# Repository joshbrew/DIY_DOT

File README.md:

# DIY Diffuse Optical Tomography (DOT) PCB plans

Testing low cost 28 sensor DOT. This repo will be getting updated as I get results and some working code to share. I will share how to drive the LEDs and how I get simultaneous sensor output as I get things demonstrable.

DIY DOT flexible sensor design based on [this 2007 Retinotopic mapping paper](https://www.pnas.org/content/104/29/12169) for a simple and modular 28 channel high-density optical tomography headset. The question I want to answer: can I get [deep image reconstruction](https://journals.plos.org/ploscompbiol/article?id=10.1371/journal.pcbi.1006633)?

This design uses 28 OPT101s and 24 pairs (48 total) 1206 sized generic LED pairs of whatever wavelength you want. The OPT101s can have the gain turned up by adding a cap and resistor between the right pins [see datasheet](https://www.ti.com/lit/ds/symlink/opt101.pdf?HQS=TI-null-null-alldatasheets-df-pf-SEP-wwe). You can get really cheap ones on Aliexpress that work consistently.

Use a site like PCBway for cheap flex PCBs. There is FR4 stiffener on both sides. This is meant to be hand-assembled, careful not to burn the pads or sensitive OPT101 pins (i.e. use low temperature solder for testing). Pop the OPT101s (notch facing left from the front) in through the back to make them flush with the stiffener and solder from back.  

# 16 channel (forehead-friendly)

New (cheapo version):

New (includes transimpedance amps):

Old:

# For LED Driver we're using the $4 RP2040 mini, drivers WIP and docs etc.

# WIP Software for capture and simulation:

3D simulation with BabylonJS:
- https://github.com/joshbrew/DIY_DOT/tree/main/js/bananas
Recording test for our nRF5x boards (WIP connector/carrier board incoming after we test it):
- https://github.com/joshbrew/DIY_DOT/tree/main/js/record_nirs

The simulation math needs help but we'll figure it out eventually.

### What you need to make it work:
* LED driver microcontroller with PWM driver, we've got a WIP firmware for the RP2040 
* 48 GPIO or some kind of relay to drive the LEDs which need to be flashed independently. Can be done by stringing multiple cheap boards together via RX/TX pins (will publish examples eventually). 
* We recommend narrow-coned LEDs to minimize scalp interference for short separation channels.
* Add light pipes over PD and LED areas to get better contact.
* [Use >1000nm IR LEDs for best penetration. (no idea if they exist at this size)](https://www.spiedigitallibrary.org/journals/journal-of-biomedical-optics/volume-25/issue-09/097003/Diffuse-correlation-spectroscopy-measurements-of-blood-flow-using-1064nm-light/10.1117/1.JBO.25.9.097003.full?fbclid=IwAR02-l_q-xCykuuqUjc_RWJfQE7ESOEIRK0G9mqZSWaGiFhfwu1QNV42vjQ&SSO=1) The other LED can be red, green, or another IR wavelength (e.g. 850nm).

## What can I do with this?

Read about fMRI, then assume this is an fMRI but it's dirt cheap in comparison. However, it only gets you the few outer centimeters of depth resolution, which can be enhanced with higher power lighting, guassian windows, interferometry (the most interesting next logical step for this ala OCT), and some other classic filtering tricks from RF and astronomy. So we can do legit mind reading, source localization for EEG, brain topology studies, and potentially real time monitoring of problems like subdural hematoma or possible metabolic issues in the high energy-demanding neocortex. Multimodal imaging promises to solve a lot of modeling problems with this technology, and there's probably a lot more to learn just in terms of how different physiology contains relevant computational information and what the interplay is. That's my very unqualified 2 cents :P

## License 
MIT License: Do whatever you want with it, I'm gonna do what I want with it too. And cite this repo if you make it useful! 
Get in touch @ brewster.joshua1@gmail.com, I'm working on a scalable version of this stuff but it just takes forever between factory times and me not knowing what the hell I'm doing.

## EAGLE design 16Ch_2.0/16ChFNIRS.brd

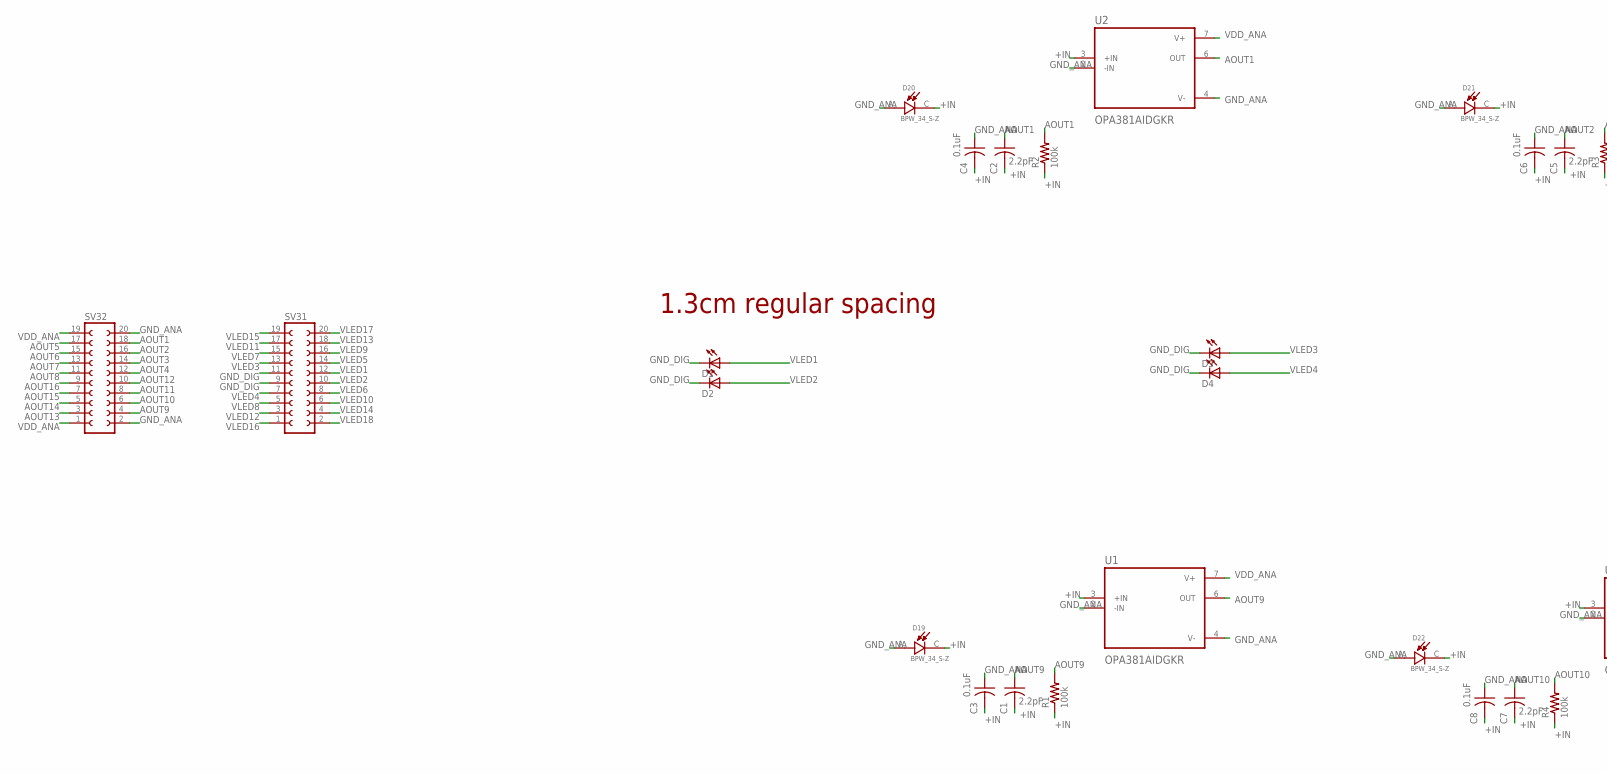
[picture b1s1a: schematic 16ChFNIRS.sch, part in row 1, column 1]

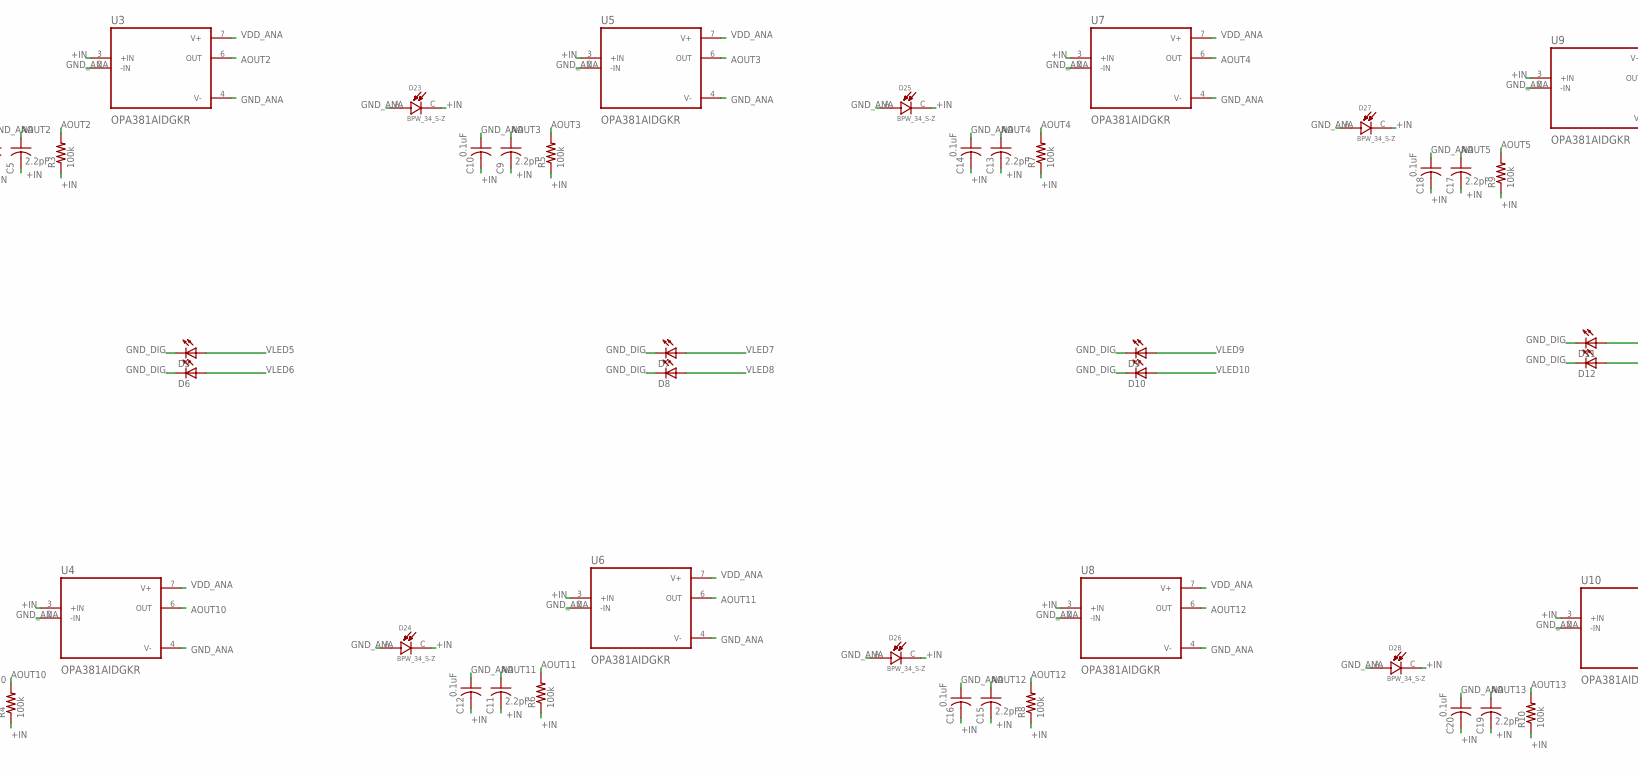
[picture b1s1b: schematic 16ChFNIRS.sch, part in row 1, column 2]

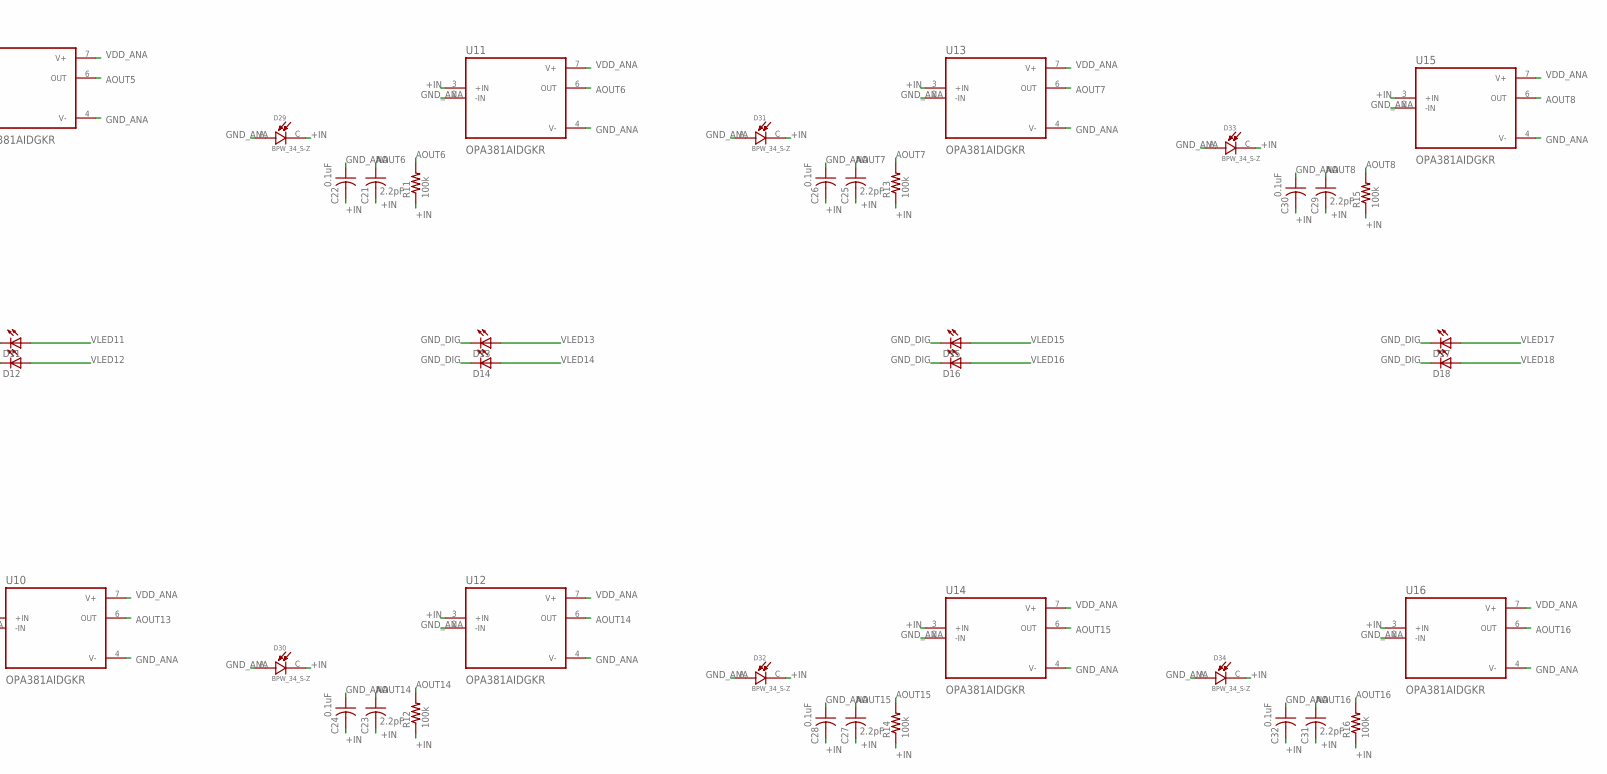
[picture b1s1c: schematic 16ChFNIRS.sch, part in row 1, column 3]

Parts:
C1, C2, C5, C7, C9, C11, C13, C15, C17, C19, C21, C23, C25, C27, C29, C31: 2.2pF; C0603K
C3, C4, C6, C8, C10, C12, C14, C16, C18, C20, C22, C24, C26, C28, C30, C32: 0.1uF; C0603K
D1, D2, D3, D4, D5, D6, D7, D8, D9, D10, D11, D12, D13, D14, D15, D16, D17, D18: LED1206; LED-1206
D19, D20, D21, D22, D23, D24, D25, D26, D27, D28, D29, D30, D31, D32, D33, D34: BPW_34_S-Z; DIO_BPW_34_S-Z
R1, R2, R3, R4, R5, R6, R7, R8, R9, R10, R11, R12, R13, R14, R15, R16: 100k; R0603
SV31, SV32: FE10-2
U1, U2, U3, U4, U5, U6, U7, U8, U9, U10, U11, U12, U13, U14, U15, U16: OPA381AIDGKR; SOP65P490X110-8N

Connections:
+IN: C1.2, C2.2, C3.2, C4.2, C5.2, C6.2, C7.2, C8.2, C9.2, C10.2, C11.2, C12.2, C13.2, C14.2, C15.2, C16.2, C17.2, C18.2, C19.2, C20.2, C21.2, C22.2, C23.2, C24.2, C25.2, C26.2, C27.2, C28.2, C29.2, C30.2, C31.2, C32.2, D19.C, D20.C, D21.C, D22.C, D23.C, D24.C, D25.C, D26.C, D27.C, D28.C, D29.C, D30.C, D31.C, D32.C, D33.C, D34.C, R1.1, R2.1, R3.1, R4.1, R5.1, R6.1, R7.1, R8.1, R9.1, R10.1, R11.1, R12.1, R13.1, R14.1, R15.1, R16.1, U1.3 (+IN), U2.3 (+IN), U3.3 (+IN), U4.3 (+IN), U5.3 (+IN), U6.3 (+IN), U7.3 (+IN), U8.3 (+IN), U9.3 (+IN), U10.3 (+IN), U11.3 (+IN), U12.3 (+IN), U13.3 (+IN), U14.3 (+IN), U15.3 (+IN), U16.3 (+IN)
AOUT1: C2.1, R2.2, SV32.18, U2.6 (OUT)
AOUT2: C5.1, R3.2, SV32.16, U3.6 (OUT)
AOUT3: C9.1, R5.2, SV32.14, U5.6 (OUT)
AOUT4: C13.1, R7.2, SV32.12, U7.6 (OUT)
AOUT5: C17.1, R9.2, SV32.17, U9.6 (OUT)
AOUT6: C21.1, R11.2, SV32.15, U11.6 (OUT)
AOUT7: C25.1, R13.2, SV32.13, U13.6 (OUT)
AOUT8: C29.1, R15.2, SV32.11, U15.6 (OUT)
AOUT9: C1.1, R1.2, SV32.4, U1.6 (OUT)
AOUT10: C7.1, R4.2, SV32.6, U4.6 (OUT)
AOUT11: C11.1, R6.2, SV32.8, U6.6 (OUT)
AOUT12: C15.1, R8.2, SV32.10, U8.6 (OUT)
AOUT13: C19.1, R10.2, SV32.3, U10.6 (OUT)
AOUT14: C23.1, R12.2, SV32.5, U12.6 (OUT)
AOUT15: C27.1, R14.2, SV32.7, U14.6 (OUT)
AOUT16: C31.1, R16.2, SV32.9, U16.6 (OUT)
GND_ANA: C3.1, C4.1, C6.1, C8.1, C10.1, C12.1, C14.1, C16.1, C18.1, C20.1, C22.1, C24.1, C26.1, C28.1, C30.1, C32.1, D19.A, D20.A, D21.A, D22.A, D23.A, D24.A, D25.A, D26.A, D27.A, D28.A, D29.A, D30.A, D31.A, D32.A, D33.A, D34.A, SV32.2, SV32.20, U1.2 (-IN), U1.4 (V-), U2.2 (-IN), U2.4 (V-), U3.2 (-IN), U3.4 (V-), U4.2 (-IN), U4.4 (V-), U5.2 (-IN), U5.4 (V-), U6.2 (-IN), U6.4 (V-), U7.2 (-IN), U7.4 (V-), U8.2 (-IN), U8.4 (V-), U9.2 (-IN), U9.4 (V-), U10.2 (-IN), U10.4 (V-), U11.2 (-IN), U11.4 (V-), U12.2 (-IN), U12.4 (V-), U13.2 (-IN), U13.4 (V-), U14.2 (-IN), U14.4 (V-), U15.2 (-IN), U15.4 (V-), U16.2 (-IN), U16.4 (V-)
GND_DIG: D1.C, D2.C, D3.C, D4.C, D5.C, D6.C, D7.C, D8.C, D9.C, D10.C, D11.C, D12.C, D13.C, D14.C, D15.C, D16.C, D17.C, D18.C, SV31.9, SV31.11
VDD_ANA: SV32.1, SV32.19, U1.7 (V+), U2.7 (V+), U3.7 (V+), U4.7 (V+), U5.7 (V+), U6.7 (V+), U7.7 (V+), U8.7 (V+), U9.7 (V+), U10.7 (V+), U11.7 (V+), U12.7 (V+), U13.7 (V+), U14.7 (V+), U15.7 (V+), U16.7 (V+)
VLED1: D1.A, SV31.12
VLED2: D2.A, SV31.10
VLED3: D3.A, SV31.13
VLED4: D4.A, SV31.7
VLED5: D5.A, SV31.14
VLED6: D6.A, SV31.8
VLED7: D7.A, SV31.15
VLED8: D8.A, SV31.5
VLED9: D9.A, SV31.16
VLED10: D10.A, SV31.6
VLED11: D11.A, SV31.17
VLED12: D12.A, SV31.3
VLED13: D13.A, SV31.18
VLED14: D14.A, SV31.4
VLED15: D15.A, SV31.19
VLED16: D16.A, SV31.1
VLED17: D17.A, SV31.20
VLED18: D18.A, SV31.2

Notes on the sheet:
1.3cm regular spacing

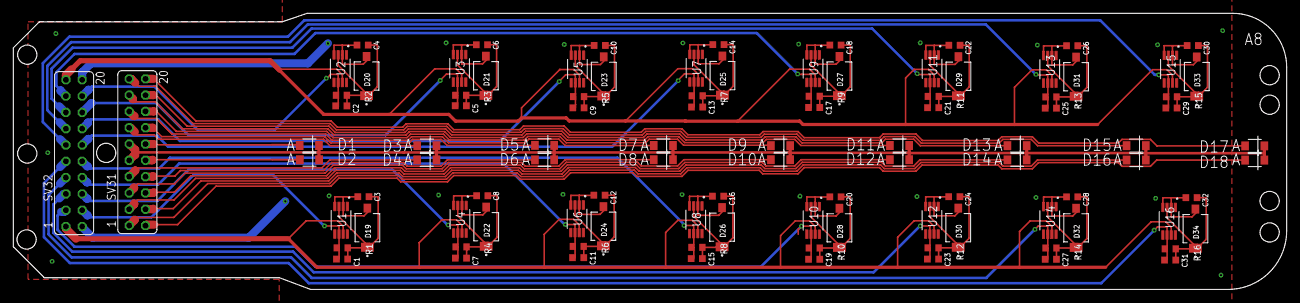
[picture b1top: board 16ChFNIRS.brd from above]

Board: 2 copper layers, 198.4 x 43.0 mm, 100 parts (0 on the bottom side), 38 nets.

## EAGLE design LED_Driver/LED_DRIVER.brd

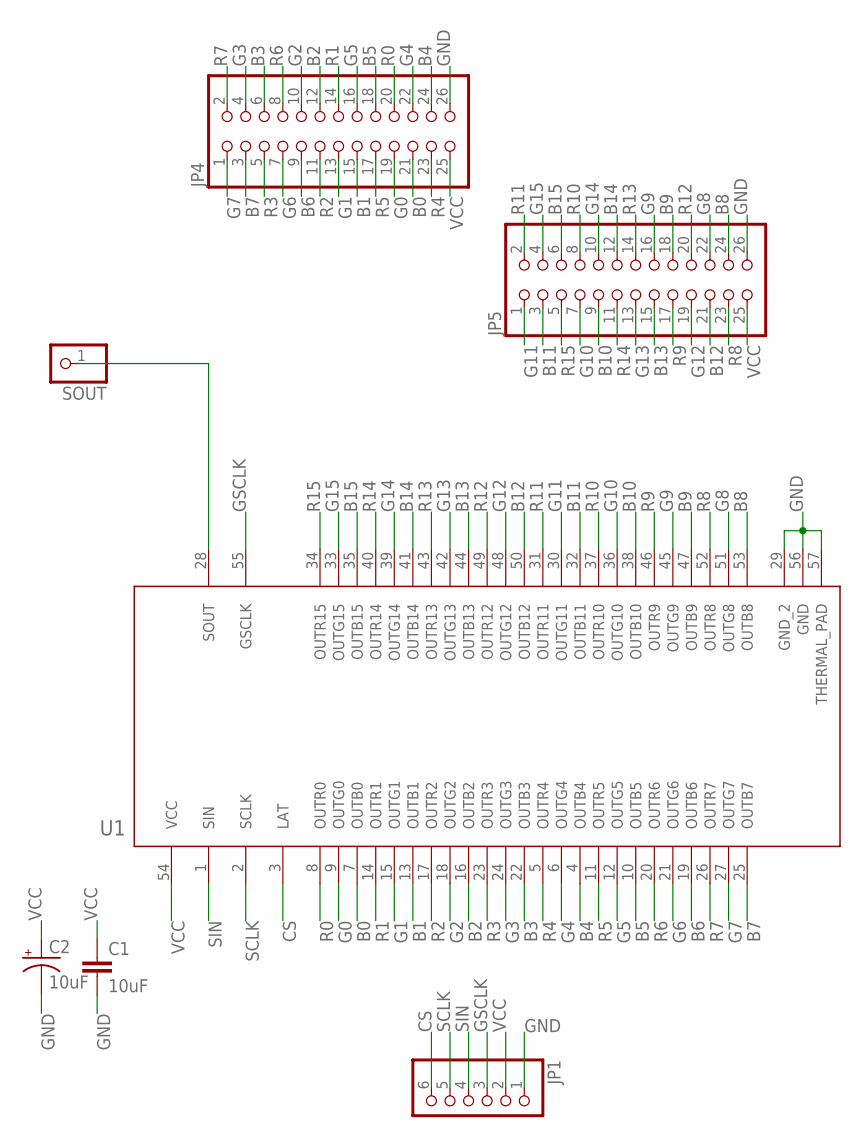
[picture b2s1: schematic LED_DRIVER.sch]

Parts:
C1: 10uF; C0603
C2: 10uF; E2-4
JP1: PINHD-1X6; 1X06
JP4, JP5: PINHD-2X13; 2X13
SOUT: PINHD-1X1; 1X01
U1: Value; DCA0056F-IPC_B

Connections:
B0: JP4.21, U1.7 (OUTB0)
B1: JP4.15, U1.13 (OUTB1)
B2: JP4.12, U1.16 (OUTB2)
B3: JP4.6, U1.22 (OUTB3)
B4: JP4.24, U1.4 (OUTB4)
B5: JP4.18, U1.10 (OUTB5)
B6: JP4.9, U1.19 (OUTB6)
B7: JP4.3, U1.25 (OUTB7)
B8: JP5.24, U1.53 (OUTB8)
B9: JP5.18, U1.47 (OUTB9)
B10: JP5.9, U1.38 (OUTB10)
B11: JP5.3, U1.32 (OUTB11)
B12: JP5.21, U1.50 (OUTB12)
B13: JP5.15, U1.44 (OUTB13)
B14: JP5.12, U1.41 (OUTB14)
B15: JP5.6, U1.35 (OUTB15)
CS: JP1.6, U1.3 (LAT)
G0: JP4.19, U1.9 (OUTG0)
G1: JP4.13, U1.15 (OUTG1)
G2: JP4.10, U1.18 (OUTG2)
G3: JP4.4, U1.24 (OUTG3)
G4: JP4.22, U1.6 (OUTG4)
G5: JP4.16, U1.12 (OUTG5)
G6: JP4.7, U1.21 (OUTG6)
G7: JP4.1, U1.27 (OUTG7)
G8: JP5.22, U1.51 (OUTG8)
G9: JP5.16, U1.45 (OUTG9)
G10: JP5.7, U1.36 (OUTG10)
G11: JP5.1, U1.30 (OUTG11)
G12: JP5.19, U1.48 (OUTG12)
G13: JP5.13, U1.42 (OUTG13)
G14: JP5.10, U1.39 (OUTG14)
G15: JP5.4, U1.33 (OUTG15)
GND: C1.2, C2.-, JP1.1, JP4.26, JP5.26, U1.29 (GND_2), U1.56 (GND), U1.57 (THERMAL_PAD)
GSCLK: JP1.3, U1.55 (GSCLK)
R0: JP4.20, U1.8 (OUTR0)
R1: JP4.14, U1.14 (OUTR1)
R2: JP4.11, U1.17 (OUTR2)
R3: JP4.5, U1.23 (OUTR3)
R4: JP4.23, U1.5 (OUTR4)
R5: JP4.17, U1.11 (OUTR5)
R6: JP4.8, U1.20 (OUTR6)
R7: JP4.2, U1.26 (OUTR7)
R8: JP5.23, U1.52 (OUTR8)
R9: JP5.17, U1.46 (OUTR9)
R10: JP5.8, U1.37 (OUTR10)
R11: JP5.2, U1.31 (OUTR11)
R12: JP5.20, U1.49 (OUTR12)
R13: JP5.14, U1.43 (OUTR13)
R14: JP5.11, U1.40 (OUTR14)
R15: JP5.5, U1.34 (OUTR15)
SCLK: JP1.5, U1.2 (SCLK)
SIN: JP1.4, U1.1 (SIN)
SOUT: SOUT.1, U1.28 (SOUT)
VCC: C1.1, C2.+, JP1.2, JP4.25, JP5.25, U1.54 (VCC)

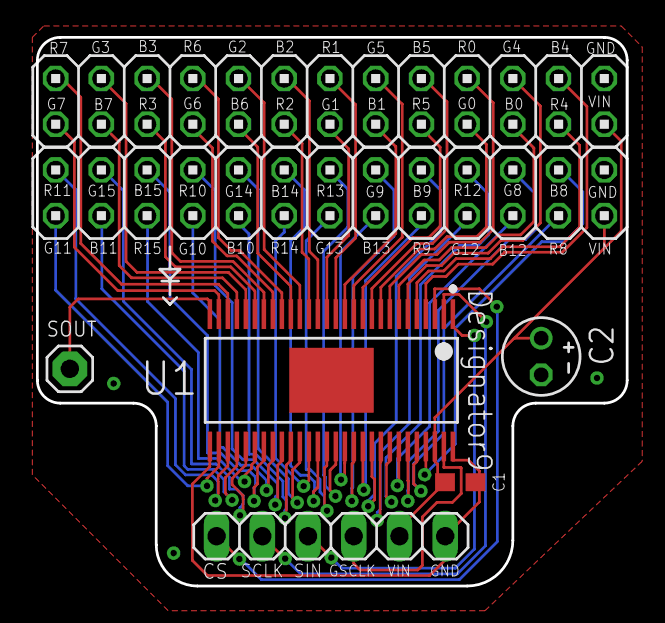
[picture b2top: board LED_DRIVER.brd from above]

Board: 2 copper layers, 32.8 x 30.5 mm, 7 parts (0 on the bottom side), 55 nets.

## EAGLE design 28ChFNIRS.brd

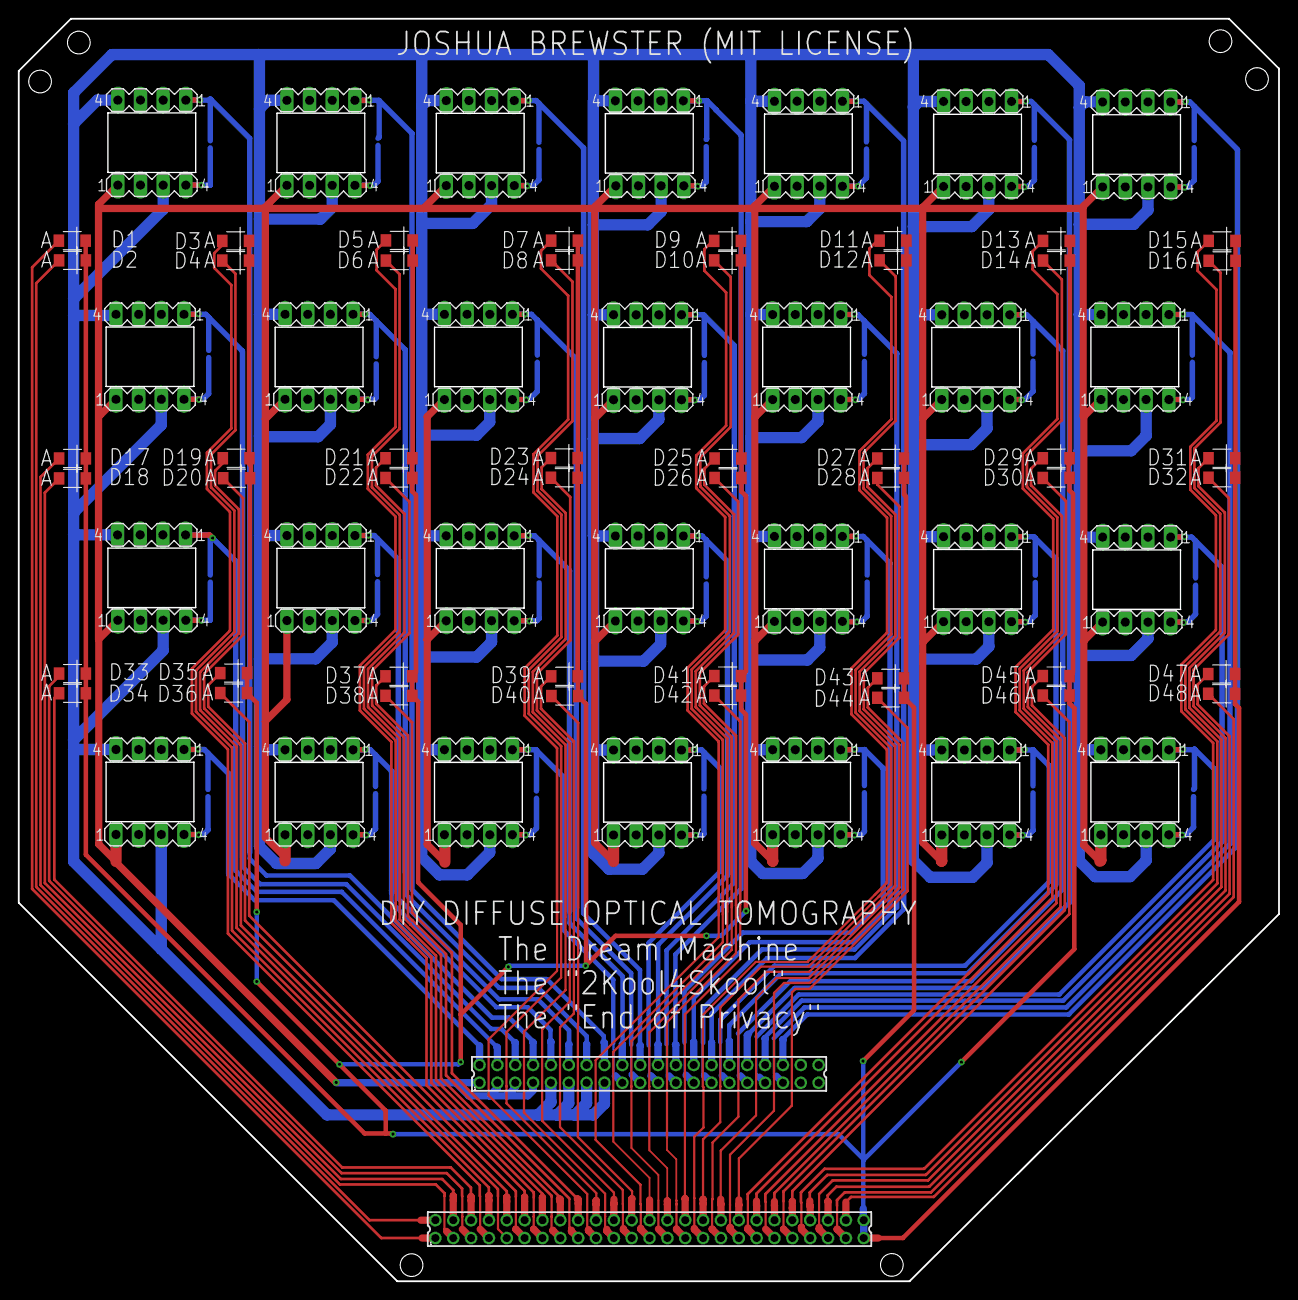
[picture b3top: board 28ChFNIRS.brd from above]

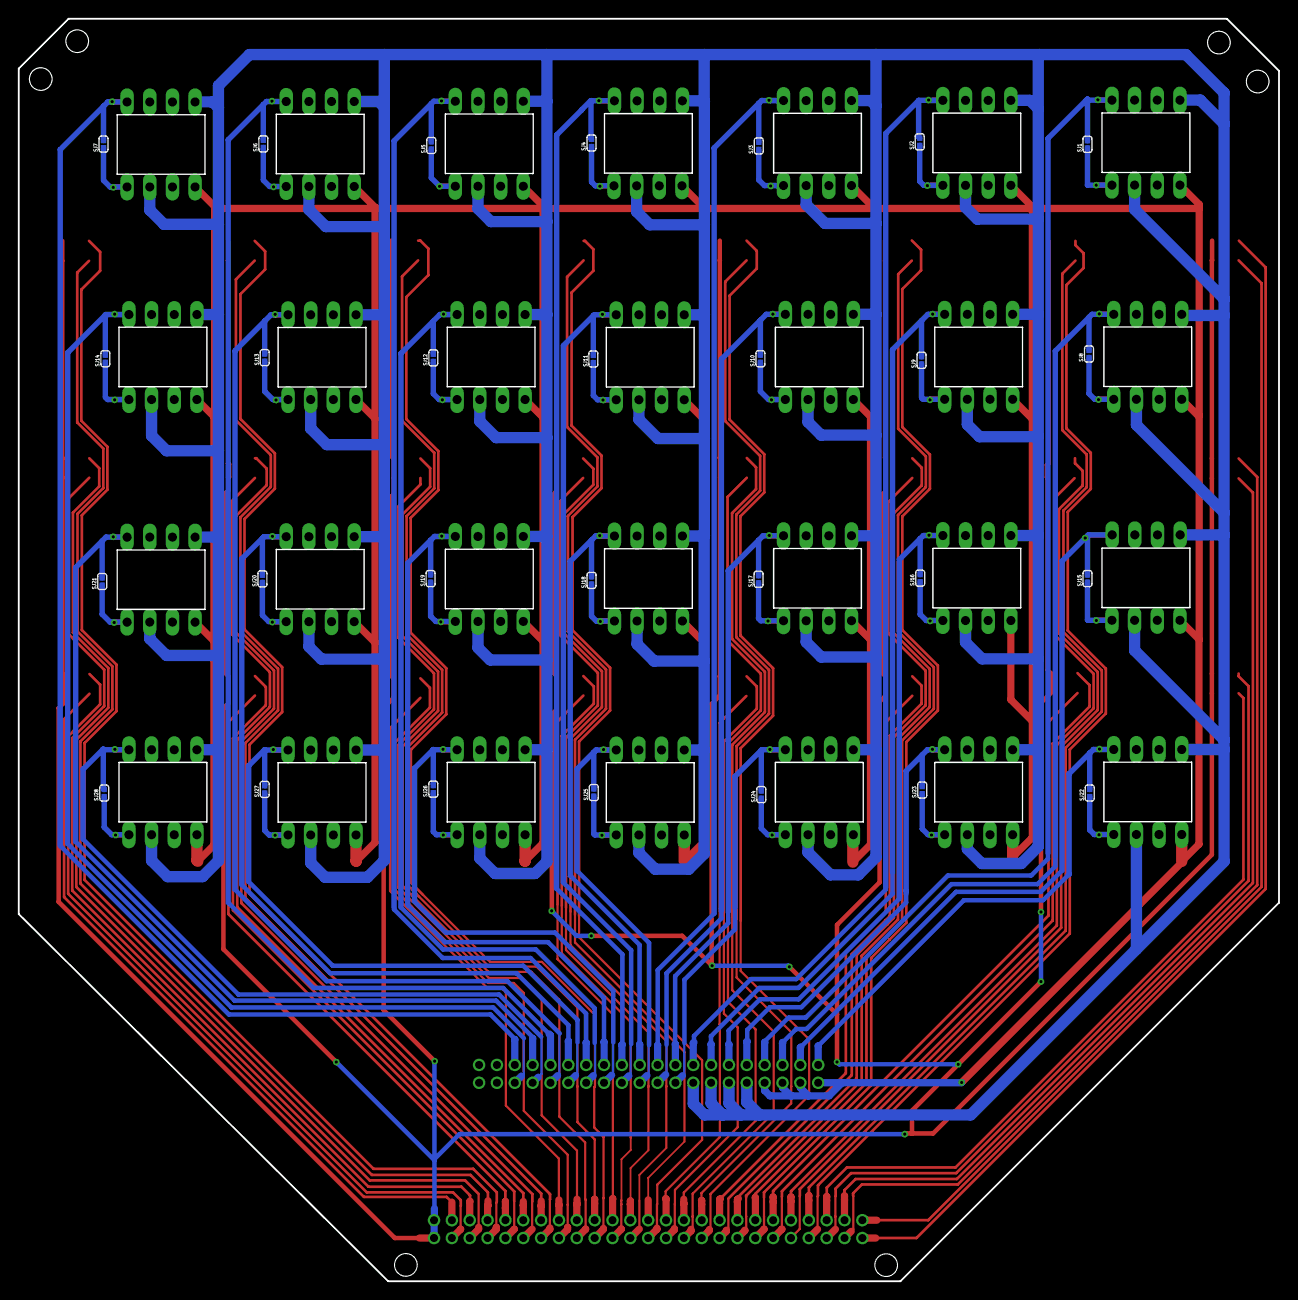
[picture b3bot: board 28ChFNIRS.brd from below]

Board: 2 copper layers, 141.2 x 141.5 mm, 134 parts (28 on the bottom side), 107 nets.

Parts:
D1, D2, D3, D4, D5, D6, D7, D8, D9, D10, D11, D12, D13, D14, D15, D16, D17, D18, D19, D20, D21, D22, D23, D24, D25, D26, D27, D28, D29, D30, D31, D32, D33, D34, D35, D36, D37, D38, D39, D40, D41, D42, D43, D44, D45, D46, D47, D48: LED-1206
SJ1, SJ2, SJ3, SJ4, SJ5, SJ6, SJ7, SJ8, SJ9, SJ10, SJ11, SJ12, SJ13, SJ14, SJ15, SJ16, SJ17, SJ18, SJ19, SJ20, SJ21, SJ22, SJ23, SJ24, SJ25, SJ26, SJ27, SJ28: SOLDERJUMPERNC; SJ_2S_SMALL
SV1, SV2, SV3, SV4, SV5, SV6, SV7, SV8, SV9, SV10, SV11, SV12, SV13, SV14, SV15, SV16, SV17, SV18, SV19, SV20, SV21, SV22, SV23, SV24, SV25, SV26, SV27, SV28, SV29, SV30, SV31, SV32, SV33, SV34, SV35, SV36, SV37, SV38, SV39, SV40, SV41, SV42, SV43, SV44, SV45, SV46, SV47, SV48, SV49, SV50, SV51, SV52, SV53, SV54, SV55, SV56: MA04-1
X1: 332-50
X2: 87758-4016

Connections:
AOUT1: SJ1.2, SV1.1, X2.8
AOUT2: SJ2.2, SV3.1, X2.16
AOUT3: SJ3.2, SV5.1, X2.20
AOUT4: SJ4.2, SV7.1, X2.24
AOUT5: SJ5.2, SV9.1, X2.28
AOUT6: SJ6.2, SV11.1, X2.32
AOUT7: SJ7.2, SV13.1, X2.36
AOUT8: SJ8.2, SV15.1, X2.6
AOUT9: SJ9.2, SV17.1, X2.14
AOUT10: SJ10.2, SV19.1, X2.19
AOUT11: SJ11.2, SV21.1, X2.23
AOUT12: SJ12.2, SV23.1, X2.27
AOUT13: SJ13.2, SV25.1, X2.31
AOUT14: SJ14.2, SV27.1, X2.35
AOUT15: SJ15.2, SV29.1, X2.4
AOUT16: SJ16.2, SV31.1, X2.12
AOUT17: SJ17.2, SV33.1, X2.18
AOUT18: SJ18.2, SV35.1, X2.22
AOUT19: SJ19.2, SV37.1, X2.26
AOUT20: SJ20.2, SV39.1, X2.30
AOUT21: SJ21.2, SV41.1, X2.34
AOUT22: SJ22.2, SV43.1, X2.2
AOUT23: SJ23.2, SV45.1, X2.10
AOUT24: SJ24.2, SV47.1, X2.17
AOUT25: SJ25.2, SV49.1, X2.21
AOUT26: SJ26.2, SV51.1, X2.25
AOUT27: SJ27.2, SV53.1, X2.29
AOUT28: SJ28.2, SV55.1, X2.33
GAIN1: SJ1.1, SV2.4
GAIN2: SJ2.1, SV4.4
GAIN3: SJ3.1, SV6.4
GAIN4: SJ4.1, SV8.4
GAIN5: SJ5.1, SV10.4
GAIN6: SJ6.1, SV12.4
GAIN7: SJ7.1, SV14.4
GAIN8: SJ8.1, SV16.4
GAIN9: SJ9.1, SV18.4
GAIN10: SJ10.1, SV20.4
GAIN11: SJ11.1, SV22.4
GAIN12: SJ12.1, SV24.4
GAIN13: SJ13.1, SV26.4
GAIN14: SJ14.1, SV28.4
GAIN15: SJ15.1, SV30.4
GAIN16: SJ16.1, SV32.4
GAIN17: SJ17.1, SV34.4
GAIN18: SJ18.1, SV36.4
GAIN19: SJ19.1, SV38.4
GAIN20: SJ20.1, SV40.4
GAIN21: SJ21.1, SV42.4
GAIN22: SJ22.1, SV44.4
GAIN23: SJ23.1, SV46.4
GAIN24: SJ24.1, SV48.4
GAIN25: SJ25.1, SV50.4
GAIN26: SJ26.1, SV52.4
GAIN27: SJ27.1, SV54.4
GAIN28: SJ28.1, SV56.4
GND_ANA: SV1.4, SV2.3, SV3.4, SV4.3, SV5.4, SV6.3, SV7.4, SV8.3, SV9.4, SV10.3, SV11.4, SV12.3, SV13.4, SV14.3, SV15.4, SV16.3, SV17.4, SV18.3, SV19.4, SV20.3, SV21.4, SV22.3, SV23.4, SV24.3, SV25.4, SV26.3, SV27.4, SV28.3, SV29.4, SV30.3, SV31.4, SV32.3, SV33.4, SV34.3, SV35.4, SV36.3, SV37.4, SV38.3, SV39.4, SV40.3, SV41.4, SV42.3, SV43.4, SV44.3, SV45.4, SV46.3, SV47.4, SV48.3, SV49.4, SV50.3, SV51.4, SV52.3, SV53.4, SV54.3, SV55.4, SV56.3, X2.9, X2.11, X2.13, X2.15
GND_DIG: D1.C, D2.C, D3.C, D4.C, D5.C, D6.C, D7.C, D8.C, D9.C, D10.C, D11.C, D12.C, D13.C, D14.C, D15.C, D16.C, D17.C, D18.C, D19.C, D20.C, D21.C, D22.C, D23.C, D24.C, D25.C, D26.C, D27.C, D28.C, D29.C, D30.C, D31.C, D32.C, D33.C, D34.C, D35.C, D36.C, D37.C, D38.C, D39.C, D40.C, D41.C, D42.C, D43.C, D44.C, D45.C, D46.C, D47.C, D48.C, X1.49, X1.50
VDD_ANA: SV2.1, SV4.1, SV6.1, SV8.1, SV10.1, SV12.1, SV14.1, SV16.1, SV18.1, SV20.1, SV22.1, SV24.1, SV26.1, SV28.1, SV30.1, SV32.1, SV34.1, SV36.1, SV38.1, SV40.1, SV42.1, SV44.1, SV46.1, SV48.1, SV50.1, SV52.1, SV54.1, SV56.1, X2.1, X2.3, X2.5, X2.7
VLED1: D1.A, X1.1
VLED2: D2.A, X1.2
VLED3: D3.A, X1.7
VLED4: D4.A, X1.8
VLED5: D5.A, X1.13
VLED6: D6.A, X1.14
VLED7: D7.A, X1.19
VLED8: D8.A, X1.20
VLED9: D9.A, X1.25
VLED10: D10.A, X1.26
VLED11: D11.A, X1.31
VLED12: D12.A, X1.32
VLED13: D13.A, X1.37
VLED14: D14.A, X1.38
VLED15: D15.A, X1.43
VLED16: D16.A, X1.44
VLED17: D17.A, X1.3
VLED18: D18.A, X1.4
VLED19: D19.A, X1.9
VLED20: D20.A, X1.10
VLED21: D21.A, X1.15
VLED22: D22.A, X1.16
VLED23: D23.A, X1.21
VLED24: D24.A, X1.22
VLED25: D25.A, X1.27
VLED26: D26.A, X1.28
VLED27: D27.A, X1.33
VLED28: D28.A, X1.34
VLED29: D29.A, X1.39
VLED30: D30.A, X1.40
VLED31: D31.A, X1.45
VLED32: D32.A, X1.46
VLED33: D33.A, X1.5
VLED34: D34.A, X1.6
VLED35: D35.A, X1.11
VLED36: D36.A, X1.12
VLED37: D37.A, X1.17
VLED38: D38.A, X1.18
VLED39: D39.A, X1.23
VLED40: D40.A, X1.24
VLED41: D41.A, X1.29
VLED42: D42.A, X1.30
VLED43: D43.A, X1.35
VLED44: D44.A, X1.36
VLED45: D45.A, X1.41
VLED46: D46.A, X1.42
VLED47: D47.A, X1.47
VLED48: D48.A, X1.48

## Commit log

2020-10-20 init repo
2021-02-18 Finished draft, time to test!
2021-02-18 added a few mounting holes
2021-06-28 16 Channel version (forehead-sized dense array)
2021-06-29 edit jumpers
2021-06-29 more stiffener
2021-07-24 add LED driver, shuffle repo
2021-07-24 rename
2023-03-26 new revisions
2023-03-28 cam files
2023-03-28 other gerbs
2023-04-14 fixed connector stiffener
2023-04-15 added wip sensor simulation
2023-04-15 edit
2023-04-15 simulates data
2023-04-16 slightly faster generation
2023-04-16 optimized to allow higher detail, biased proportions out
2023-04-16 added bias to proportions to favor the crest of the wave for better vis
2023-04-16 bananas
2023-04-17 add a flat view
2023-04-24 vastly speed up voxel gen step
2023-04-24 plane x and y positions are weird
2023-05-05 add a recording test

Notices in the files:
16Ch_2.0/16ChFNIRS.brd:
JOSHUA BREWSTER (MIT LICENSE)
